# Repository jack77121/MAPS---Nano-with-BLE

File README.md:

# MAPS-Arduino Nano
![Image of PCB layout]
(https://github.com/jack77121/MAPS---Nano-with-BLE/blob/master/MAPS_BLE_appearance.png)

## Story
**M**icro **A**ir **P**ollution **S**ensing - MAPS

Air pollution is a hot topic in recent years, especially - **Particulate Matter**. Traditional sensing method, we can only depend on professional sensors/devices, with large volume, heave weight and insanity price.
Thanks to the technology, now we could build our own air pollution sensing station, with micro volume, light weight and the price is affordable :). With MAPS, you can sense air pollution any where, any time by yourself, you can also give it a battery module to increase its mobility!

For more air pollution sensing project, you can visit [LASS facebook](https://www.facebook.com/groups/1607718702812067/) and [LASS github](https://github.com/LinkItONEDevGroup/LASS), we are makers who sense anything in our environment!

## Hardware & Sensors
Module      |	Description
------------|--------------
Arduino Nano|Mainboard
RTC         |time sync
BLE         |pair with smart phone
G3 (pms3003)|Particalute matter (PM)
DHT22       |Temperature & humidity
BMP180      |Ambient pressure
IRC-A1      |CO<sub>2</sub>

## PCB layout & dimensions
![Image of pcb layout]
(https://github.com/jack77121/MAPS---Nano-with-BLE/blob/master/PCB_layout.png)

(unit: mm)

## Installation
1. Upload *MAPS_BLE.ino* to your nano.
2. Compile and install *MAPS_ble* to android phone.
3. Choose to pair the MAPS BLE module from app.
4. You are ready to see the sensors data on you phone.

![Image of app after pairing]
(https://github.com/jack77121/MAPS---Nano-with-BLE/blob/master/app_figure.png)

## Notes
* I use 3 LEDs to show the CO<sub>2</sub> and PM level, whether its safe (green: PM<sub>2.5</sub> <= 32 and CO<sub>2</sub> <= 1000), warning (orange: 32 < PM<sub>2.5</sub> <= 53) and danger (red: PM<sub>2.5</sub> >53 or CO<sub>2</sub> > 1000)
* BLE module use grove universal sockets, can easily replace with your favorite module (maybe a data logger instead), just beware that the socket is connect to **5v power**. 
* ESP-01 socket is preserve for esp8266 module extension, it's fine to leave it if you don't need it.

## Reviews
1. IRC-A1 is a good sensor for CO<sub>2</sub> sensing, but with great power, you also need great skill to use it. You need to add operational amplifier (OPA) in your circuit, infact, most of my circuit and components are for the IRC-A1, include TLC271cp (OPA), IRF520 (MOSFET) and several resistor & capacitor. You also need to calibrate it, with ZERO gas (0 ppm CO<sub>2</sub>) and fix-concentration target gas (for me, 1000 ppm CO<sub>2</sub>).
I think the better circuit should use an external power with low-dropout (LDO) regulator as its power source, and use a crystal oscillator to trigger it (like it mention in its spec, but in this project, I use arduino PWM library to simulate the duty cycle it needs, maybe that's why I cannnot get the best result) .
2. The polygon of GND should not be that large, because it transfers the heat, and it will affect the DHT22 accuracy.

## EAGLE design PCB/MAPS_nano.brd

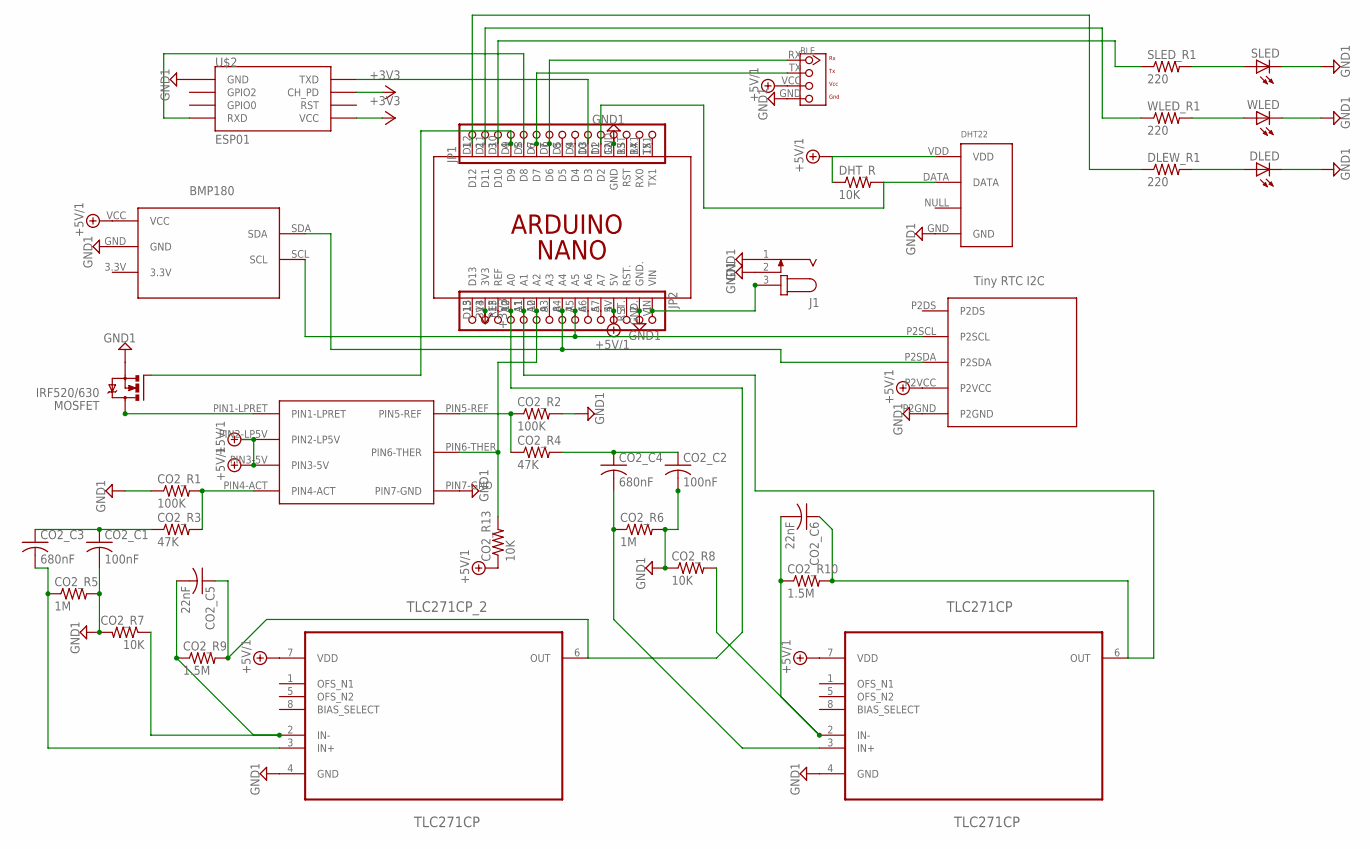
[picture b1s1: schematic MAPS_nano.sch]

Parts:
BMP180: BMP180
CO2_C1, CO2_C2: 100nF; C0805
CO2_C3, CO2_C4: 680nF; C0805
CO2_C5, CO2_C6: 22nF; C0805
CO2_R1, CO2_R2: 100K; R0805
CO2_R3, CO2_R4: 47K; R0805
CO2_R5, CO2_R6: 1M; R0805
CO2_R7, CO2_R8, CO2_R13: 10K; R0805
CO2_R9, CO2_R10: 1.5M; R0805
DHT_R: 10K; R0805
DLED: LED5MM
DLEW_R1: 220; R0805
J1: JACK-PLUG0; SPC4077
J2: TWIG-4P-2.0-2.0; 4P-2.0
JP1, JP2: PINHD-1X15-CB; 1X15-CB
MOSFET: IRF520/630; TO220BH
PCB1: ARDUINO_NANO
SLED: LED5MM
SLED_R1: 220; R0805
TLC271CP, TLC271CP_2: TLC271CP; DIP254P762X508-8
U1: RHT03_DHT-22_AM2302RA; RHT03_DHT-22/RA
U$1: IRC-A1; ALPHASENSE
U$2: ESP01
U$3: RTC_TINY_IIC
WLED: LED5MM
WLED_R1: 220; R0805

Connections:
+3V3: JP2.14, PCB1.3V3, U$2.CH_PD, U$2.VCC
+5V/1: BMP180.VCC, CO2_R13.1, DHT_R.1, J2.VCC, JP2.4, PCB1.5V, TLC271CP.7 (VDD), TLC271CP_2.7 (VDD), U1.VDD, U$1.PIN2-LP5V, U$1.PIN3-5V, U$3.P2VCC
GND1: BMP180.GND, CO2_C1.2, CO2_C2.2, CO2_R1.1, CO2_R2.2, CO2_R5.2, CO2_R6.2, CO2_R7.2, CO2_R8.1, DLED.K (C), J1.1, J1.2, J2.GND, JP1.12, JP2.2, MOSFET.S, PCB1.GND, PCB1.GND., SLED.K (C), TLC271CP.4 (GND), TLC271CP_2.4 (GND), U1.GND, U$1.PIN7-GND, U$2.GND, U$3.P2GND, WLED.K (C)
unnamed: DHT_R.2, JP1.11, PCB1.D2, U1.DATA
unnamed: J1.3, JP2.1, PCB1.VIN
unnamed: JP1.4, MOSFET.G, PCB1.D9
unnamed: MOSFET.D, U$1.PIN1-LPRET
unnamed: CO2_R13.2, JP2.10, PCB1.A2, U$1.PIN6-THER
unnamed: BMP180.SDA, JP2.8, PCB1.A4, U$3.P2SDA
unnamed: BMP180.SCL, JP2.7, PCB1.A5, U$3.P2SCL
unnamed: CO2_C1.1, CO2_C3.1, CO2_R3.1
unnamed: CO2_R1.2, CO2_R3.2, U$1.PIN4-ACT
unnamed: CO2_C3.2, CO2_R5.1, TLC271CP_2.3 (IN+)
unnamed: CO2_C5.2, CO2_R7.1, CO2_R9.1, TLC271CP_2.2 (IN-)
unnamed: CO2_C5.1, CO2_R9.2, JP2.12, PCB1.A0, TLC271CP_2.6 (OUT)
unnamed: DLEW_R1.1, JP1.1, PCB1.D12
unnamed: CO2_R2.1, CO2_R4.1, U$1.PIN5-REF
unnamed: CO2_C2.1, CO2_C4.1, CO2_R4.2
unnamed: CO2_C4.2, CO2_R6.1, TLC271CP.3 (IN+)
unnamed: JP1.2, PCB1.D11, WLED_R1.1
unnamed: JP1.3, PCB1.D10, SLED_R1.1
unnamed: CO2_C6.2, CO2_R8.2, CO2_R10.1, TLC271CP.2 (IN-)
unnamed: SLED.A, SLED_R1.2
unnamed: JP1.5, PCB1.D8, U$2.RX (RXD)
unnamed: J2.RX, JP1.7, PCB1.D6
unnamed: J2.TX, JP1.6, PCB1.D7
unnamed: CO2_C6.1, CO2_R10.2, JP2.11, PCB1.A1, TLC271CP.6 (OUT)
unnamed: JP1.8, PCB1.D5
unnamed: JP1.9, PCB1.D4
unnamed: JP1.10, PCB1.D3, U$2.TX (TXD)
unnamed: JP1.13, PCB1.RST
unnamed: JP1.14, PCB1.RX1 (RX0)
unnamed: JP1.15, PCB1.TX1
unnamed: JP2.3, PCB1.RST.
unnamed: JP2.5, PCB1.A7
unnamed: JP2.6, PCB1.A6
unnamed: JP2.9, PCB1.A3
unnamed: JP2.13, PCB1.REF
unnamed: JP2.15, PCB1.D13
unnamed: WLED.A, WLED_R1.2
unnamed: DLED.A, DLEW_R1.2

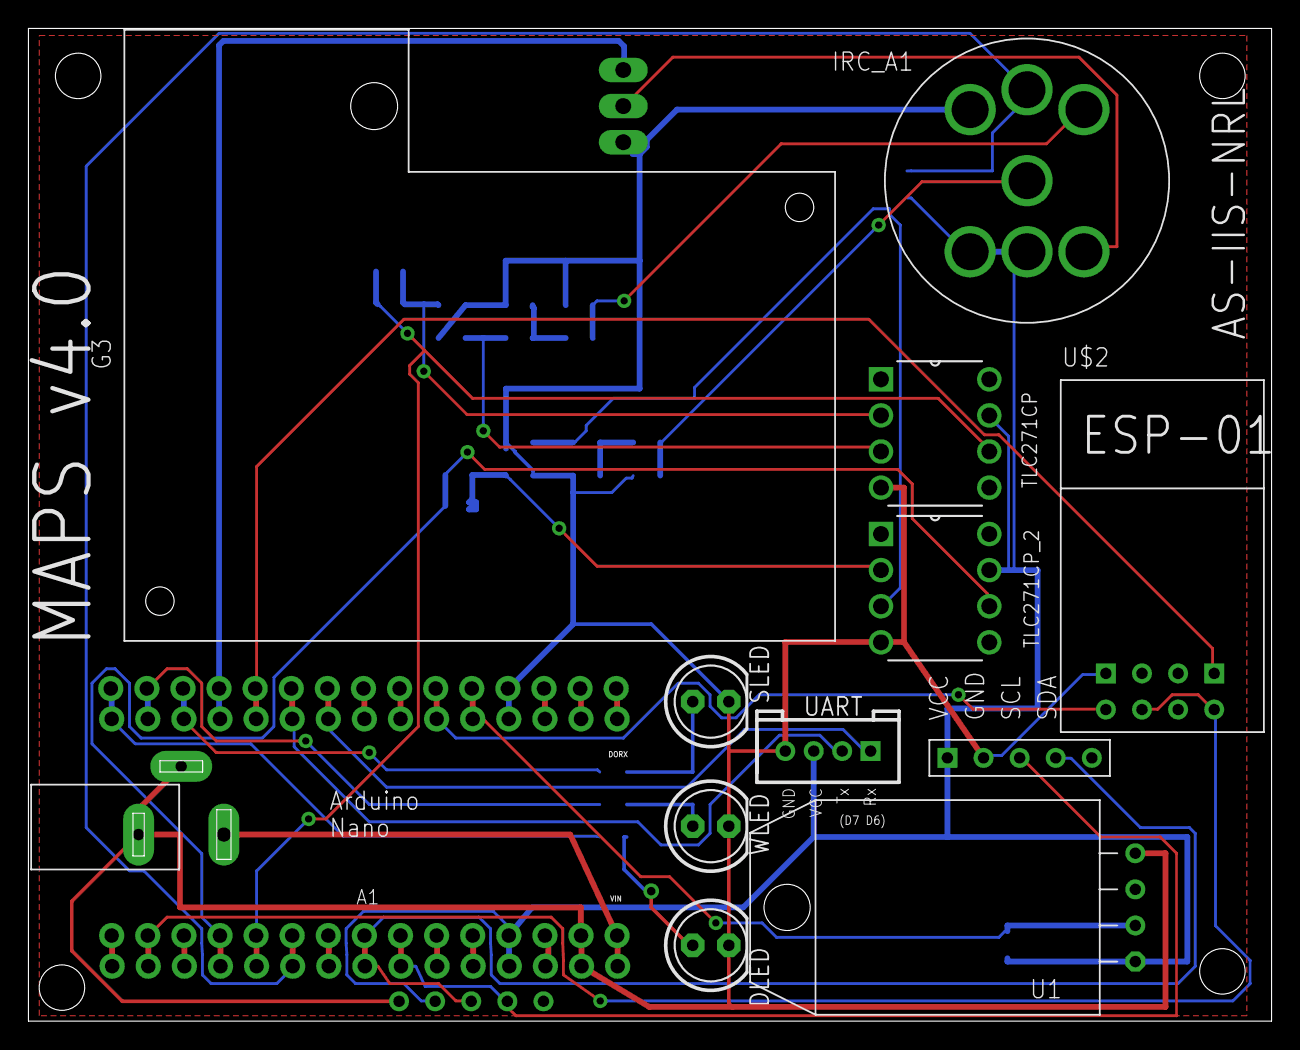
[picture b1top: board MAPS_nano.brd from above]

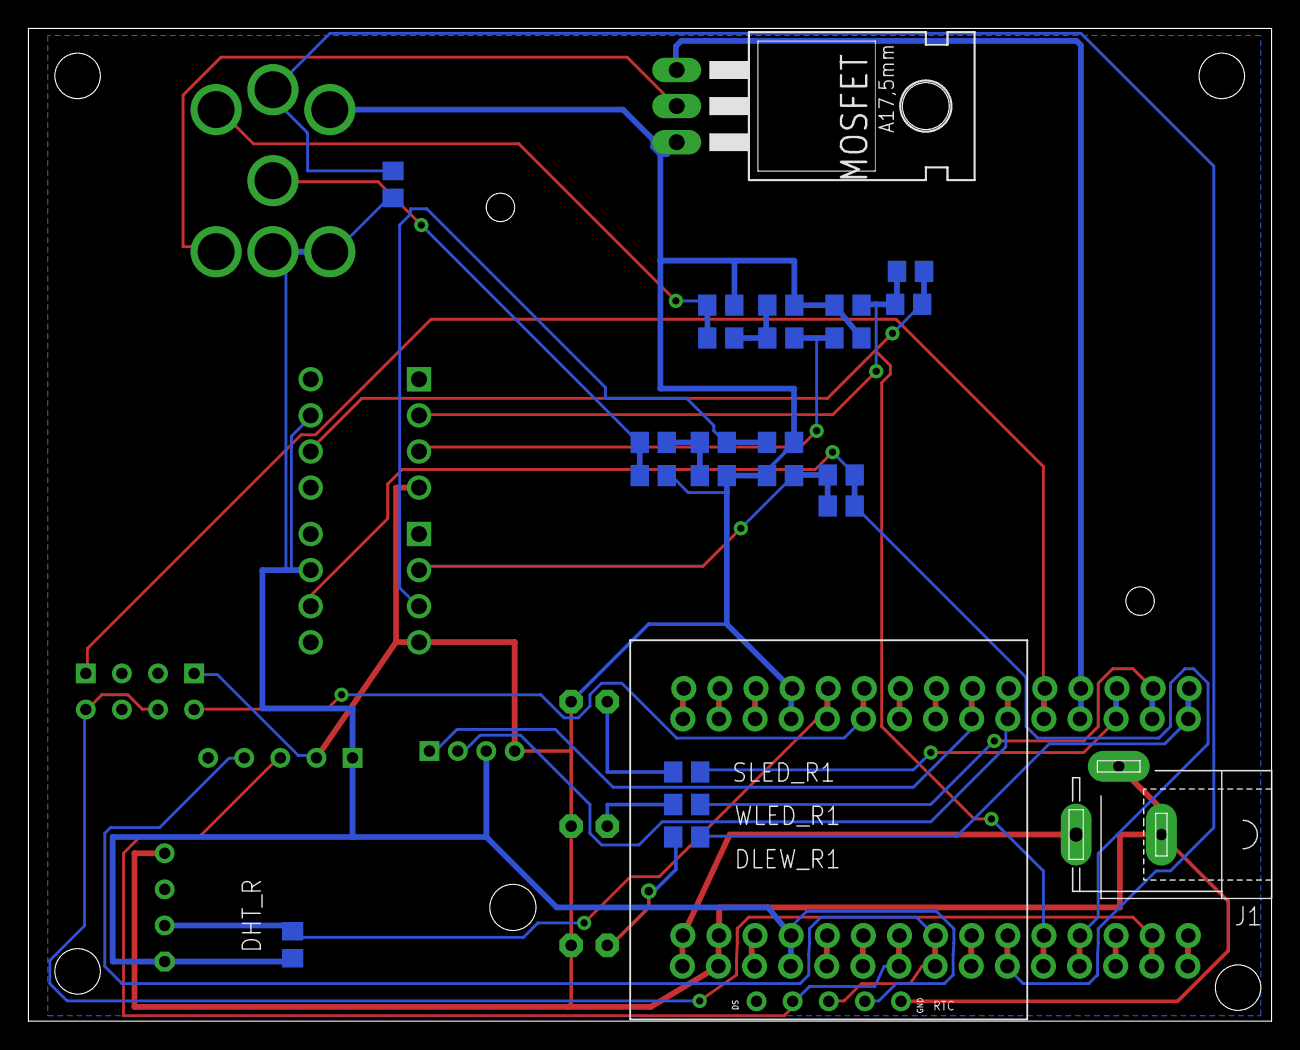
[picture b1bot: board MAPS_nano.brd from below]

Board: 2 copper layers, 87.5 x 69.8 mm, 38 parts (24 on the bottom side), 41 nets.

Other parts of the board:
U$4: G3

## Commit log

2016-09-17 update README pcb layout figure
2016-09-17 code revise, add comment
2016-09-17 android app, using Android Studio, edit from hm10 android sample code
2016-09-21 update readme & upload appearance figure
2016-09-25 update readme & figure
